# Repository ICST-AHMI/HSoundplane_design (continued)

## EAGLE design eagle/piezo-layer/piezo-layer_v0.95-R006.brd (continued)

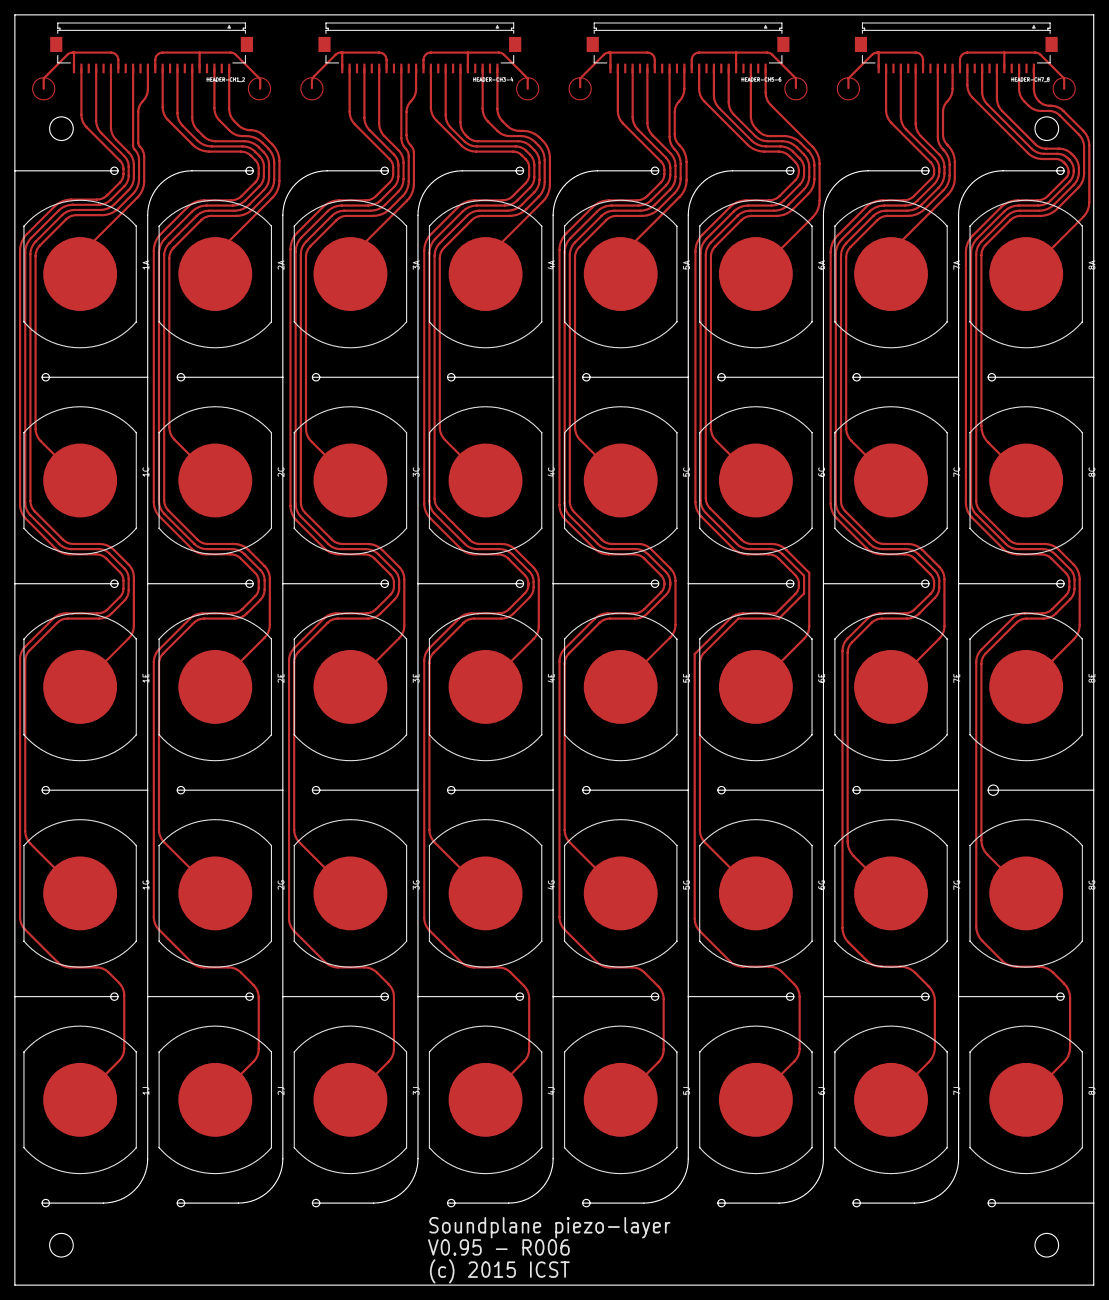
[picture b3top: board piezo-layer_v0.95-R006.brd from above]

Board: 2 copper layers, 146.0 x 171.9 mm, 44 parts (0 on the bottom side), 48 nets.

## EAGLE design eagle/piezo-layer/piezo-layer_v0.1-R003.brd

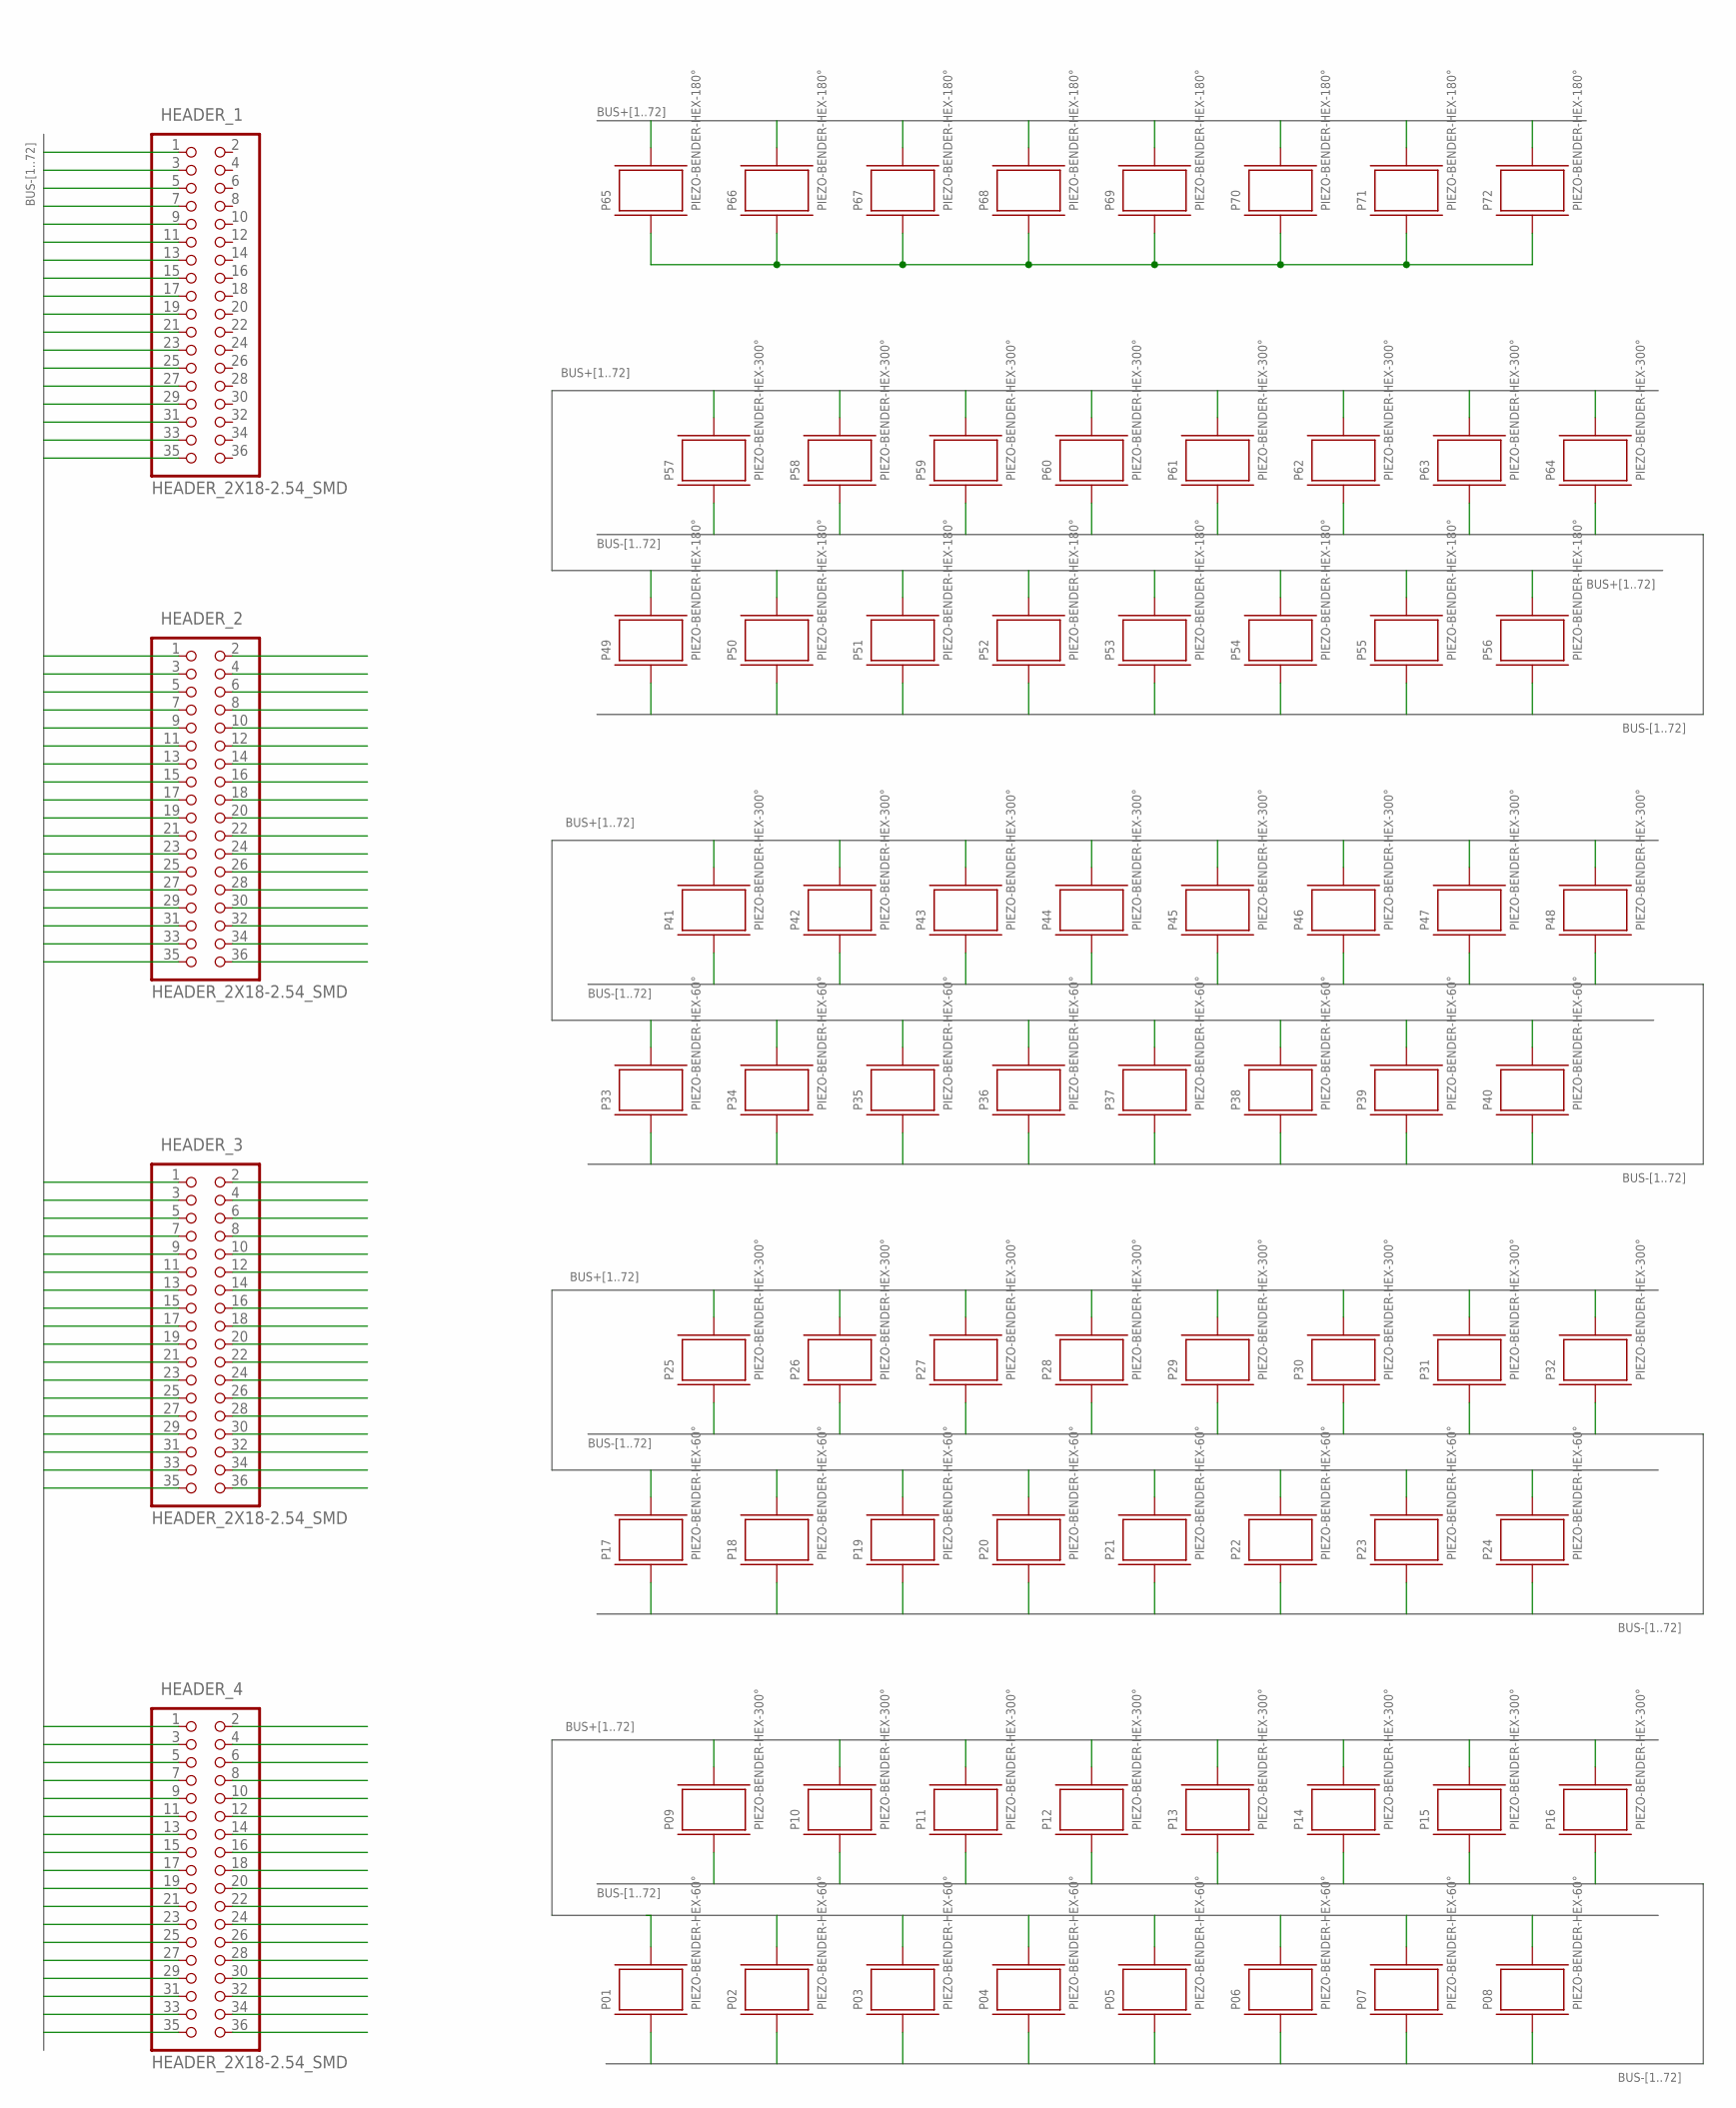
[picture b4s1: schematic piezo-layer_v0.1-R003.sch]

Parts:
HEADER_1, HEADER_2, HEADER_3, HEADER_4: HEADER_2X18-2.54_SMD; 2X18_2.54_SMD
P01, P02, P03, P04, P05, P06, P07, P08, P17, P18, P19, P20, P21, P22, P23, P24, P33, P34, P35, P36, P37, P38, P39, P40: PIEZO-BENDER-HEX-60°; PIEZO-BENDER-HEX_16MM_60°
P09, P10, P11, P12, P13, P14, P15, P16, P25, P26, P27, P28, P29, P30, P31, P32, P41, P42, P43, P44, P45, P46, P47, P48, P57, P58, P59, P60, P61, P62, P63, P64: PIEZO-BENDER-HEX-300°; PIEZO-BENDER-HEX_16MM_300°
P49, P50, P51, P52, P53, P54, P55, P56, P65, P66, P67, P68, P69, P70, P71, P72: PIEZO-BENDER-HEX-180°; PIEZO-BENDER-HEX_16MM_180°

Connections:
BUS+1: P01.TIP1 (+_1)
BUS+2: P02.TIP1 (+_1)
BUS+3: HEADER_2.18, P03.TIP1 (+_1)
BUS+4: HEADER_2.36, P04.TIP1 (+_1)
BUS+5: HEADER_3.18, P05.TIP1 (+_1)
BUS+6: HEADER_3.36, P06.TIP1 (+_1)
BUS+7: HEADER_4.18, P07.TIP1 (+_1)
BUS+8: HEADER_4.36, P08.TIP1 (+_1)
BUS+9: P09.TIP1 (+_1)
BUS+10: P10.TIP1 (+_1)
BUS+11: HEADER_2.16, P11.TIP1 (+_1)
BUS+12: HEADER_2.34, P12.TIP1 (+_1)
BUS+13: HEADER_3.16, P13.TIP1 (+_1)
BUS+14: HEADER_3.34, P14.TIP1 (+_1)
BUS+15: HEADER_4.16, P15.TIP1 (+_1)
BUS+16: HEADER_4.34, P16.TIP1 (+_1)
BUS+17: P17.TIP1 (+_1)
BUS+18: P18.TIP1 (+_1)
BUS+19: HEADER_2.14, P19.TIP1 (+_1)
BUS+20: HEADER_2.32, P20.TIP1 (+_1)
BUS+21: HEADER_3.14, P21.TIP1 (+_1)
BUS+22: HEADER_3.32, P22.TIP1 (+_1)
BUS+23: HEADER_4.14, P23.TIP1 (+_1)
BUS+24: HEADER_4.32, P24.TIP1 (+_1)
BUS+25: P25.TIP1 (+_1)
BUS+26: P26.TIP1 (+_1)
BUS+27: HEADER_2.12, P27.TIP1 (+_1)
BUS+28: HEADER_2.30, P28.TIP1 (+_1)
BUS+29: HEADER_3.12, P29.TIP1 (+_1)
BUS+30: HEADER_3.30, P30.TIP1 (+_1)
BUS+31: HEADER_4.12, P31.TIP1 (+_1)
BUS+32: HEADER_4.30, P32.TIP1 (+_1)
BUS+33: P33.TIP1 (+_1)
BUS+34: P34.TIP1 (+_1)
BUS+35: HEADER_2.10, P35.TIP1 (+_1)
BUS+36: HEADER_2.28, P36.TIP1 (+_1)
BUS+37: HEADER_3.10, P37.TIP1 (+_1)
BUS+38: HEADER_3.28, P38.TIP1 (+_1)
BUS+39: HEADER_4.10, P39.TIP1 (+_1)
BUS+40: HEADER_4.28, P40.TIP1 (+_1)
BUS+41: P41.TIP1 (+_1)
BUS+42: P42.TIP1 (+_1)
BUS+43: HEADER_2.8, P43.TIP1 (+_1)
BUS+44: HEADER_2.26, P44.TIP1 (+_1)
BUS+45: HEADER_3.8, P45.TIP1 (+_1)
BUS+46: HEADER_3.26, P46.TIP1 (+_1)
BUS+47: HEADER_4.8, P47.TIP1 (+_1)
BUS+48: HEADER_4.26, P48.TIP1 (+_1)
BUS+49: P49.TIP1 (+_1)
BUS+50: P50.TIP1 (+_1)
BUS+51: HEADER_2.6, P51.TIP1 (+_1)
BUS+52: HEADER_2.24, P52.TIP1 (+_1)
BUS+53: HEADER_3.6, P53.TIP1 (+_1)
BUS+54: HEADER_3.24, P54.TIP1 (+_1)
BUS+55: HEADER_4.6, P55.TIP1 (+_1)
BUS+56: HEADER_4.24, P56.TIP1 (+_1)
BUS+57: P57.TIP1 (+_1)
BUS+58: P58.TIP1 (+_1)
BUS+59: HEADER_2.4, P59.TIP1 (+_1)
BUS+60: HEADER_2.22, P60.TIP1 (+_1)
BUS+61: HEADER_3.4, P61.TIP1 (+_1)
BUS+62: HEADER_3.22, P62.TIP1 (+_1)
BUS+63: HEADER_4.4, P63.TIP1 (+_1)
BUS+64: HEADER_4.22, P64.TIP1 (+_1)
BUS+65: P65.TIP1 (+_1)
BUS+66: P66.TIP1 (+_1)
BUS+67: HEADER_2.2, P67.TIP1 (+_1)
BUS+68: HEADER_2.20, P68.TIP1 (+_1)
BUS+69: HEADER_3.2, P69.TIP1 (+_1)
BUS+70: HEADER_3.20, P70.TIP1 (+_1)
BUS+71: HEADER_4.2, P71.TIP1 (+_1)
BUS+72: HEADER_4.20, P72.TIP1 (+_1)
BUS-1: HEADER_1.17, P01.PAD1 (-_1)
BUS-2: HEADER_1.35, P02.PAD1 (-_1)
BUS-3: HEADER_2.17, P03.PAD1 (-_1)
BUS-4: HEADER_2.35, P04.PAD1 (-_1)
BUS-5: HEADER_3.17, P05.PAD1 (-_1)
BUS-6: HEADER_3.35, P06.PAD1 (-_1)
BUS-7: HEADER_4.17, P07.PAD1 (-_1)
BUS-8: HEADER_4.35, P08.PAD1 (-_1)
BUS-9: HEADER_1.15, P09.PAD1 (-_1)
BUS-10: HEADER_1.33, P10.PAD1 (-_1)
BUS-11: HEADER_2.15, P11.PAD1 (-_1)
BUS-12: HEADER_2.33, P12.PAD1 (-_1)
BUS-13: HEADER_3.15, P13.PAD1 (-_1)
BUS-14: HEADER_3.33, P14.PAD1 (-_1)
BUS-15: HEADER_4.15, P15.PAD1 (-_1)
BUS-16: HEADER_4.33, P16.PAD1 (-_1)
BUS-17: HEADER_1.13, P17.PAD1 (-_1)
BUS-18: HEADER_1.31, P18.PAD1 (-_1)
BUS-19: HEADER_2.13, P19.PAD1 (-_1)
BUS-20: HEADER_2.31, P20.PAD1 (-_1)
BUS-21: HEADER_3.13, P21.PAD1 (-_1)
BUS-22: HEADER_3.31, P22.PAD1 (-_1)
BUS-23: HEADER_4.13, P23.PAD1 (-_1)
BUS-24: HEADER_4.31, P24.PAD1 (-_1)
BUS-25: HEADER_1.11, P25.PAD1 (-_1)
BUS-26: HEADER_1.29, P26.PAD1 (-_1)
BUS-27: HEADER_2.11, P27.PAD1 (-_1)
BUS-28: HEADER_2.29, P28.PAD1 (-_1)
BUS-29: HEADER_3.11, P29.PAD1 (-_1)
BUS-30: HEADER_3.29, P30.PAD1 (-_1)
BUS-31: HEADER_4.11, P31.PAD1 (-_1)
BUS-32: HEADER_4.29, P32.PAD1 (-_1)
BUS-33: HEADER_1.9, P33.PAD1 (-_1)
BUS-34: HEADER_1.27, P34.PAD1 (-_1)
BUS-35: HEADER_2.9, P35.PAD1 (-_1)
BUS-36: HEADER_2.27, P36.PAD1 (-_1)
BUS-37: HEADER_3.9, P37.PAD1 (-_1)
BUS-38: HEADER_3.27, P38.PAD1 (-_1)
BUS-39: HEADER_4.9, P39.PAD1 (-_1)
BUS-40: HEADER_4.27, P40.PAD1 (-_1)
BUS-41: HEADER_1.7, P41.PAD1 (-_1)
BUS-42: HEADER_1.25, P42.PAD1 (-_1)
BUS-43: HEADER_2.7, P43.PAD1 (-_1)
BUS-44: HEADER_2.25, P44.PAD1 (-_1)
BUS-45: HEADER_3.7, P45.PAD1 (-_1)
BUS-46: HEADER_3.25, P46.PAD1 (-_1)
BUS-47: HEADER_4.7, P47.PAD1 (-_1)
BUS-48: HEADER_4.25, P48.PAD1 (-_1)
BUS-49: HEADER_1.5, P49.PAD1 (-_1)
BUS-50: HEADER_1.23, P50.PAD1 (-_1)
BUS-51: HEADER_2.5, P51.PAD1 (-_1)
BUS-52: HEADER_2.23, P52.PAD1 (-_1)
BUS-53: HEADER_3.5, P53.PAD1 (-_1)
BUS-54: HEADER_3.23, P54.PAD1 (-_1)
BUS-55: HEADER_4.5, P55.PAD1 (-_1)
BUS-56: HEADER_4.23, P56.PAD1 (-_1)
BUS-57: HEADER_1.3, P57.PAD1 (-_1)
BUS-58: HEADER_1.21, P58.PAD1 (-_1)
BUS-59: HEADER_2.3, P59.PAD1 (-_1)
BUS-60: HEADER_2.21, P60.PAD1 (-_1)
BUS-61: HEADER_3.3, P61.PAD1 (-_1)
BUS-62: HEADER_3.21, P62.PAD1 (-_1)
BUS-63: HEADER_4.3, P63.PAD1 (-_1)
BUS-64: HEADER_4.21, P64.PAD1 (-_1)
BUS-65: HEADER_1.1
BUS-66: HEADER_1.19
BUS-67: HEADER_2.1
BUS-68: HEADER_2.19
BUS-69: HEADER_3.1
BUS-70: HEADER_3.19, P65.PAD1 (-_1), P66.PAD1 (-_1), P67.PAD1 (-_1), P68.PAD1 (-_1), P69.PAD1 (-_1), P70.PAD1 (-_1), P71.PAD1 (-_1), P72.PAD1 (-_1)
BUS-71: HEADER_4.1
BUS-72: HEADER_4.19

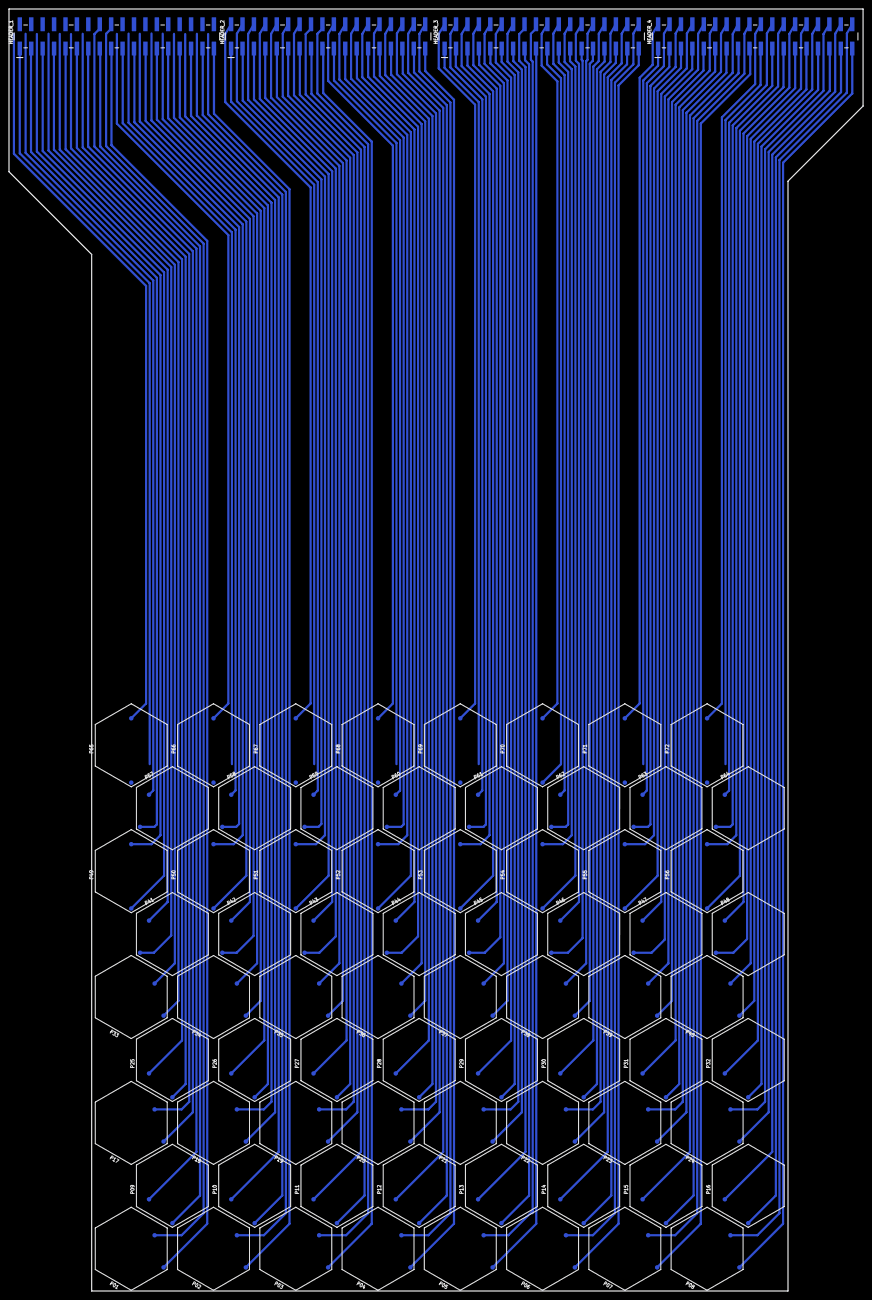
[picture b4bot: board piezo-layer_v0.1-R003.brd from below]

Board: 1 copper layer, 190.0 x 285.2 mm, 76 parts (76 on the bottom side), 119 nets.

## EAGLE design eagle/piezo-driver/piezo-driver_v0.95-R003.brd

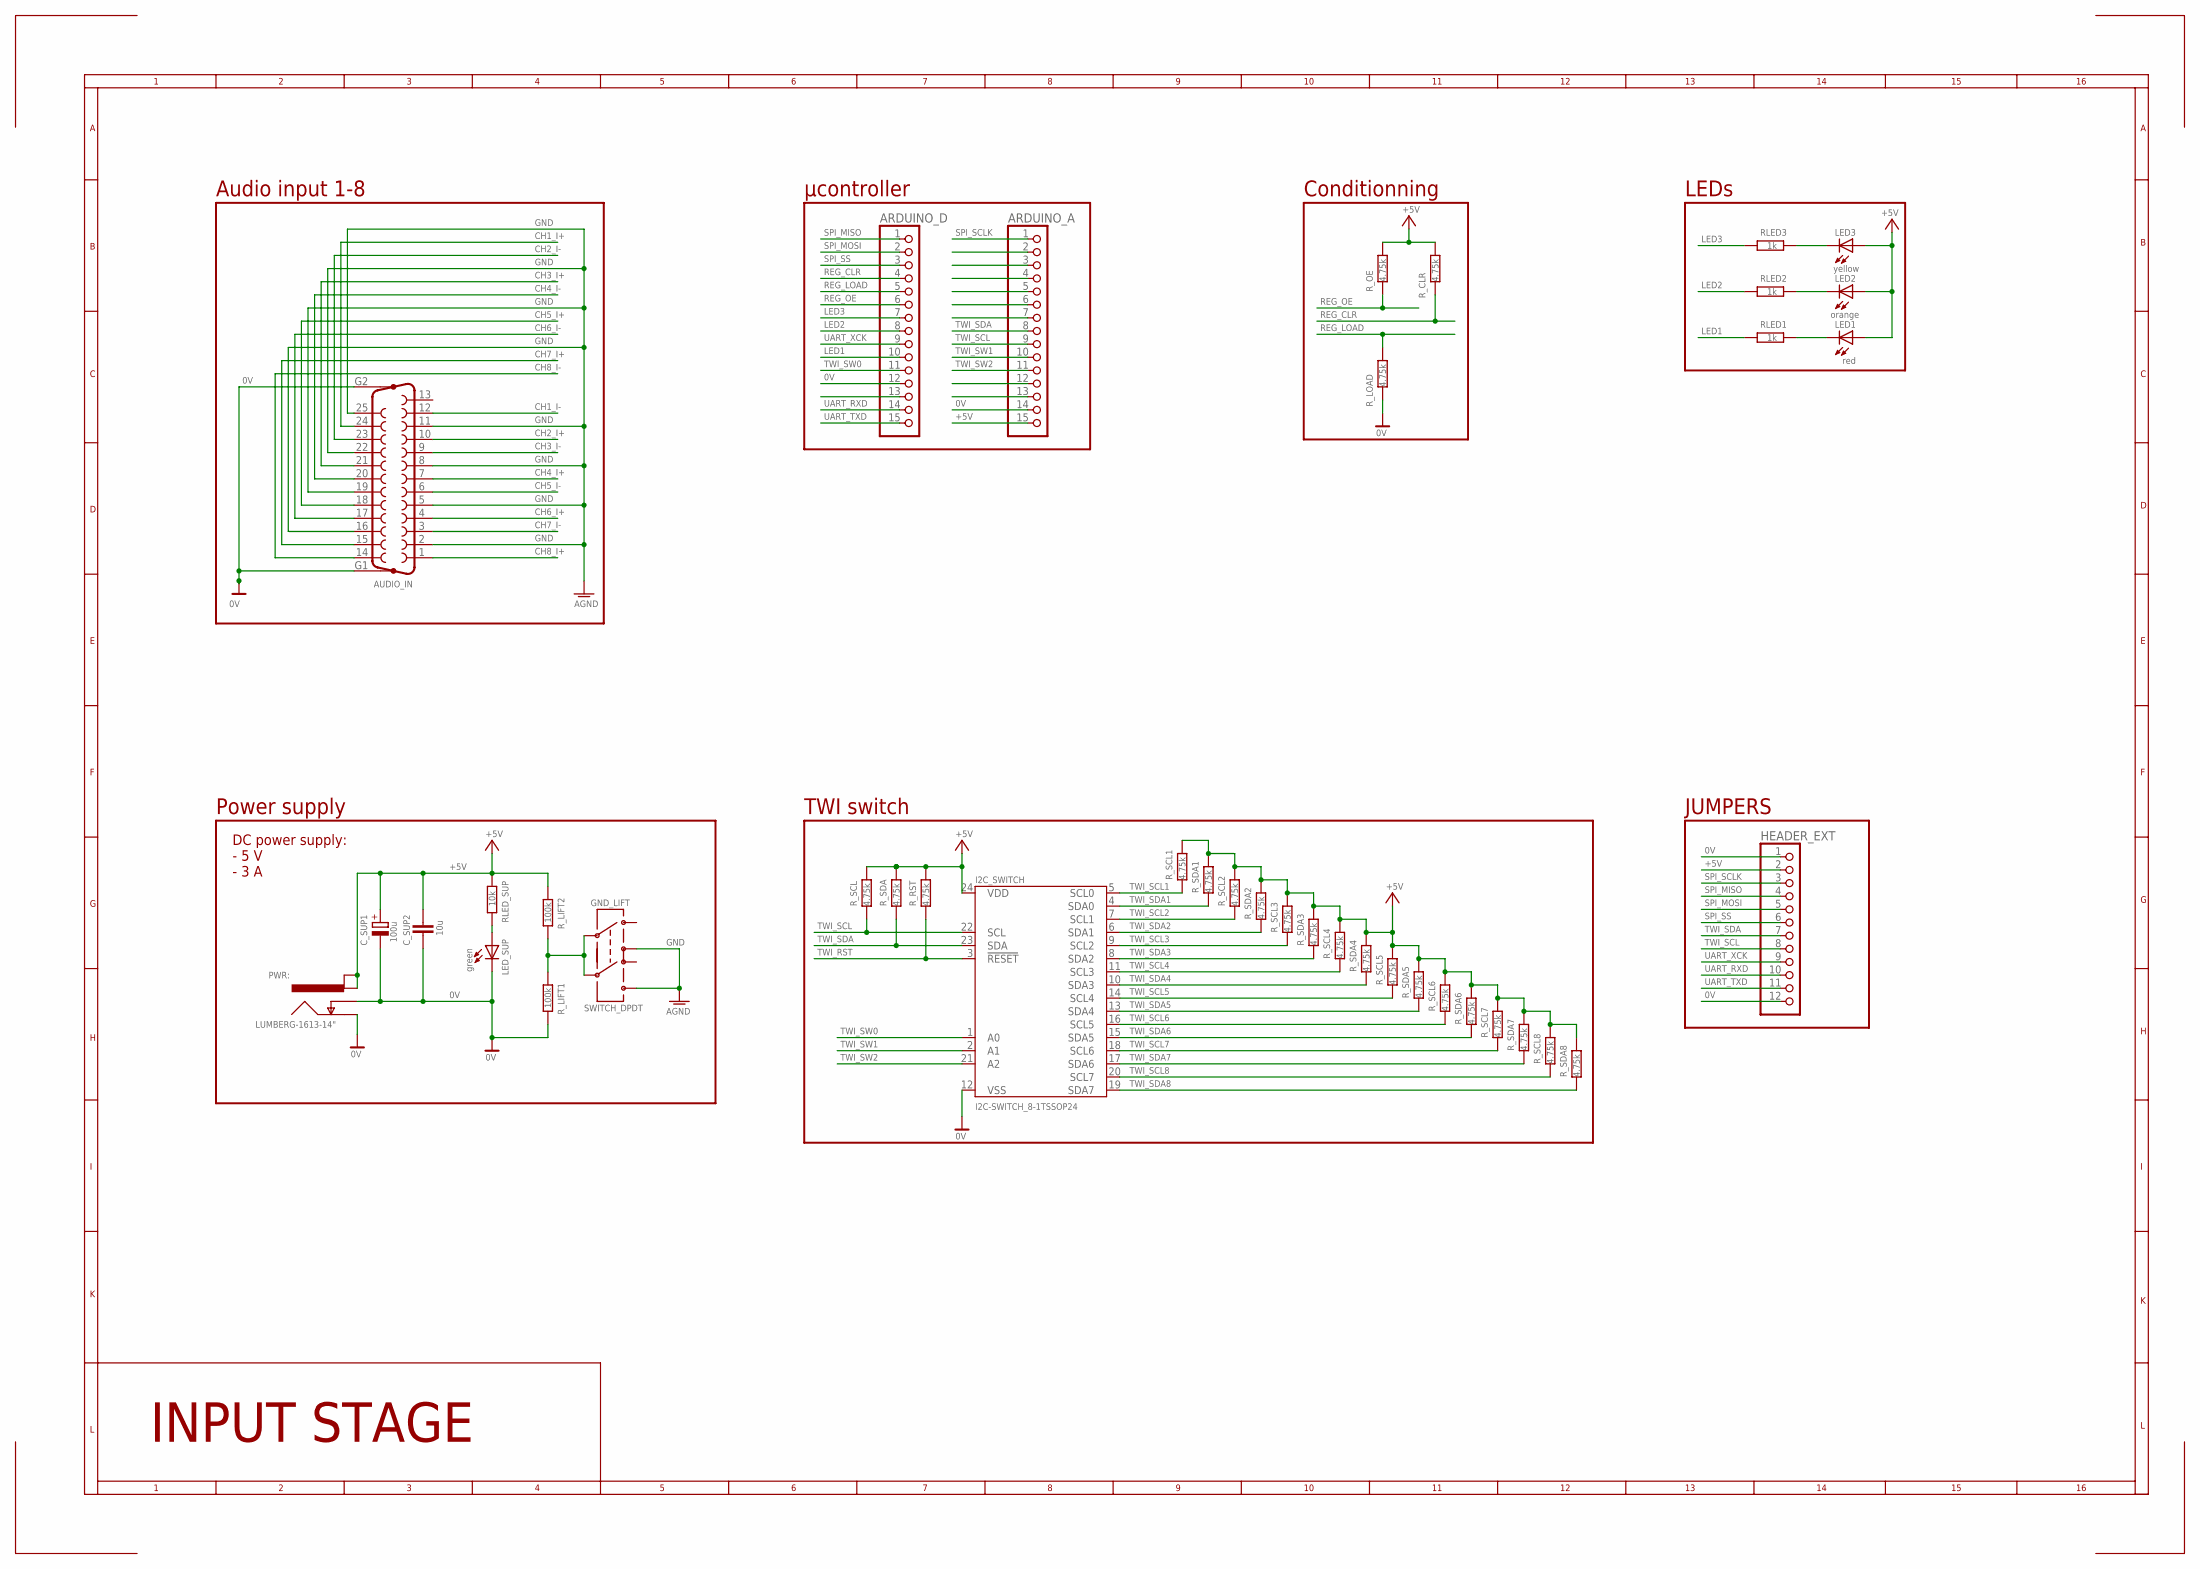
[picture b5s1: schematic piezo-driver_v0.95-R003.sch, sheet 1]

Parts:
ARDUINO_A: PINHD-1X15; 1X15
ARDUINO_D: PINHD-1X15; 1X15
AUDIO_IN: F25HP
C_SUP1: 100u; EIA3216
C_SUP2: 10u; C0805K
GND_LIFT: SWITCH_DPDT; SWITCH_JS202011
HEADER_EXT: PINHD-1X12; 1X12
I2C_SWITCH: I2C-SWITCH_8-1TSSOP24; TSSOP24
LED1: red; LED-1206
LED2: orange; LED-1206
LED3: yellow; LED-1206
LED_SUP: green; LED-1206
PWR:: LUMBERG-1613-14"; LUMBERG-1613_14
RLED1, RLED2, RLED3: 1k; R0402
RLED_SUP: 10k; R0402
R_CLR: 4.75k; R0402
R_LIFT1, R_LIFT2: 100k; R0402
R_LOAD: 4.75k; R0402
R_OE: 4.75k; R0402
R_RST: 4.75k; R0402
R_SCL, R_SCL1, R_SCL2, R_SCL3, R_SCL4, R_SCL5, R_SCL6, R_SCL7, R_SCL8: 4.75k; R0402
R_SDA, R_SDA1, R_SDA2, R_SDA3, R_SDA4, R_SDA5, R_SDA6, R_SDA7, R_SDA8: 4.75k; R0402

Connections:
0V: ARDUINO_A.14, ARDUINO_D.12, AUDIO_IN.G1, AUDIO_IN.G2, C_SUP1.C (-), C_SUP2.2, HEADER_EXT.1, HEADER_EXT.12, I2C_SWITCH.12 (VSS), LED_SUP.C, PWR:.1 (GND), PWR:.2 (GND_INS), R_LIFT1.1, R_LOAD.1; also elsewhere on the board
+5V: ARDUINO_A.15, C_SUP1.A (+), C_SUP2.1, HEADER_EXT.2, I2C_SWITCH.24 (VDD), LED1.A, LED2.A, LED3.A, PWR:.3 (PWR_1), PWR:.4 (PWR_2), RLED_SUP.2, R_CLR.2, R_LIFT2.2, R_OE.2, R_RST.2, R_SCL.2, R_SCL1.2, R_SCL2.2, R_SCL3.2, R_SCL4.2, R_SCL5.2, R_SCL6.2, R_SCL7.2, R_SCL8.2, R_SDA.2, R_SDA1.2, R_SDA2.2, R_SDA3.2, R_SDA4.2, R_SDA5.2, R_SDA6.2, R_SDA7.2, R_SDA8.2; also elsewhere on the board
A_3V3: ARDUINO_A.2
A_5V: ARDUINO_A.12
A_A0: ARDUINO_A.4
A_A1: ARDUINO_A.5
A_A2: ARDUINO_A.6
A_A3: ARDUINO_A.7
A_REF: ARDUINO_A.3
A_RST1: ARDUINO_D.13
A_RST2: ARDUINO_A.13
CH1_I+: AUDIO_IN.24; also elsewhere on the board
CH1_I-: AUDIO_IN.12; also elsewhere on the board
CH2_I+: AUDIO_IN.10; also elsewhere on the board
CH2_I-: AUDIO_IN.23; also elsewhere on the board
CH3_I+: AUDIO_IN.21; also elsewhere on the board
CH3_I-: AUDIO_IN.9; also elsewhere on the board
CH4_I+: AUDIO_IN.7; also elsewhere on the board
CH4_I-: AUDIO_IN.20; also elsewhere on the board
CH5_I+: AUDIO_IN.18; also elsewhere on the board
CH5_I-: AUDIO_IN.6; also elsewhere on the board
CH6_I+: AUDIO_IN.4; also elsewhere on the board
CH6_I-: AUDIO_IN.17; also elsewhere on the board
CH7_I+: AUDIO_IN.15; also elsewhere on the board
CH7_I-: AUDIO_IN.3; also elsewhere on the board
CH8_I+: AUDIO_IN.1; also elsewhere on the board
CH8_I-: AUDIO_IN.14; also elsewhere on the board
GND: AUDIO_IN.2, AUDIO_IN.5, AUDIO_IN.8, AUDIO_IN.11, AUDIO_IN.16, AUDIO_IN.19, AUDIO_IN.22, AUDIO_IN.25, GND_LIFT.1 (T1A), GND_LIFT.6 (T2A)
LED1: ARDUINO_D.10, RLED1.1
LED2: ARDUINO_D.8, RLED2.1
LED3: ARDUINO_D.7, RLED3.1
unnamed: LED_SUP.A, RLED_SUP.1
unnamed: LED3.C, RLED3.2
unnamed: LED2.C, RLED2.2
unnamed: LED1.C, RLED1.2
unnamed: GND_LIFT.2 (P1), GND_LIFT.5 (P2), R_LIFT1.2, R_LIFT2.1
REG_CLR: ARDUINO_D.4, R_CLR.1; also elsewhere on the board
REG_LOAD: ARDUINO_D.5, R_LOAD.2; also elsewhere on the board
REG_OE: ARDUINO_D.6, R_OE.1; also elsewhere on the board
SPI_MISO: ARDUINO_D.1, HEADER_EXT.4
SPI_MOSI: ARDUINO_D.2, HEADER_EXT.5; also elsewhere on the board
SPI_SCLK: ARDUINO_A.1, HEADER_EXT.3; also elsewhere on the board
SPI_SS: ARDUINO_D.3, HEADER_EXT.6
TWI_RST: I2C_SWITCH.3 (!RESET), R_RST.1
TWI_SCL: ARDUINO_A.9, HEADER_EXT.8, I2C_SWITCH.22 (SCL), R_SCL.1
TWI_SCL1: I2C_SWITCH.5 (SCL0), R_SCL1.1; also elsewhere on the board
TWI_SCL2: I2C_SWITCH.7 (SCL1), R_SCL2.1; also elsewhere on the board
TWI_SCL3: I2C_SWITCH.9 (SCL2), R_SCL3.1; also elsewhere on the board
TWI_SCL4: I2C_SWITCH.11 (SCL3), R_SCL4.1; also elsewhere on the board
TWI_SCL5: I2C_SWITCH.14 (SCL4), R_SCL5.1; also elsewhere on the board
TWI_SCL6: I2C_SWITCH.16 (SCL5), R_SCL6.1; also elsewhere on the board
TWI_SCL7: I2C_SWITCH.18 (SCL6), R_SCL7.1; also elsewhere on the board
TWI_SCL8: I2C_SWITCH.20 (SCL7), R_SCL8.1; also elsewhere on the board
TWI_SDA: ARDUINO_A.8, HEADER_EXT.7, I2C_SWITCH.23 (SDA), R_SDA.1
TWI_SDA1: I2C_SWITCH.4 (SDA0), R_SDA1.1; also elsewhere on the board
TWI_SDA2: I2C_SWITCH.6 (SDA1), R_SDA2.1; also elsewhere on the board
TWI_SDA3: I2C_SWITCH.8 (SDA2), R_SDA3.1; also elsewhere on the board
TWI_SDA4: I2C_SWITCH.10 (SDA3), R_SDA4.1; also elsewhere on the board
TWI_SDA5: I2C_SWITCH.13 (SDA4), R_SDA5.1; also elsewhere on the board
TWI_SDA6: I2C_SWITCH.15 (SDA5), R_SDA6.1; also elsewhere on the board
TWI_SDA7: I2C_SWITCH.17 (SDA6), R_SDA7.1; also elsewhere on the board
TWI_SDA8: I2C_SWITCH.19 (SDA7), R_SDA8.1; also elsewhere on the board
TWI_SW0: ARDUINO_D.11, I2C_SWITCH.1 (A0)
TWI_SW1: ARDUINO_A.10, I2C_SWITCH.2 (A1)
TWI_SW2: ARDUINO_A.11, I2C_SWITCH.21 (A2)
UART_RXD: ARDUINO_D.14, HEADER_EXT.10
UART_TXD: ARDUINO_D.15, HEADER_EXT.11
UART_XCK: ARDUINO_D.9, HEADER_EXT.9

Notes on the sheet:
Audio input 1-8
Power supply
DC power supply: - 5 V - 3 A
INPUT STAGE
µcontroller
LEDs
JUMPERS
TWI switch
Conditionning
